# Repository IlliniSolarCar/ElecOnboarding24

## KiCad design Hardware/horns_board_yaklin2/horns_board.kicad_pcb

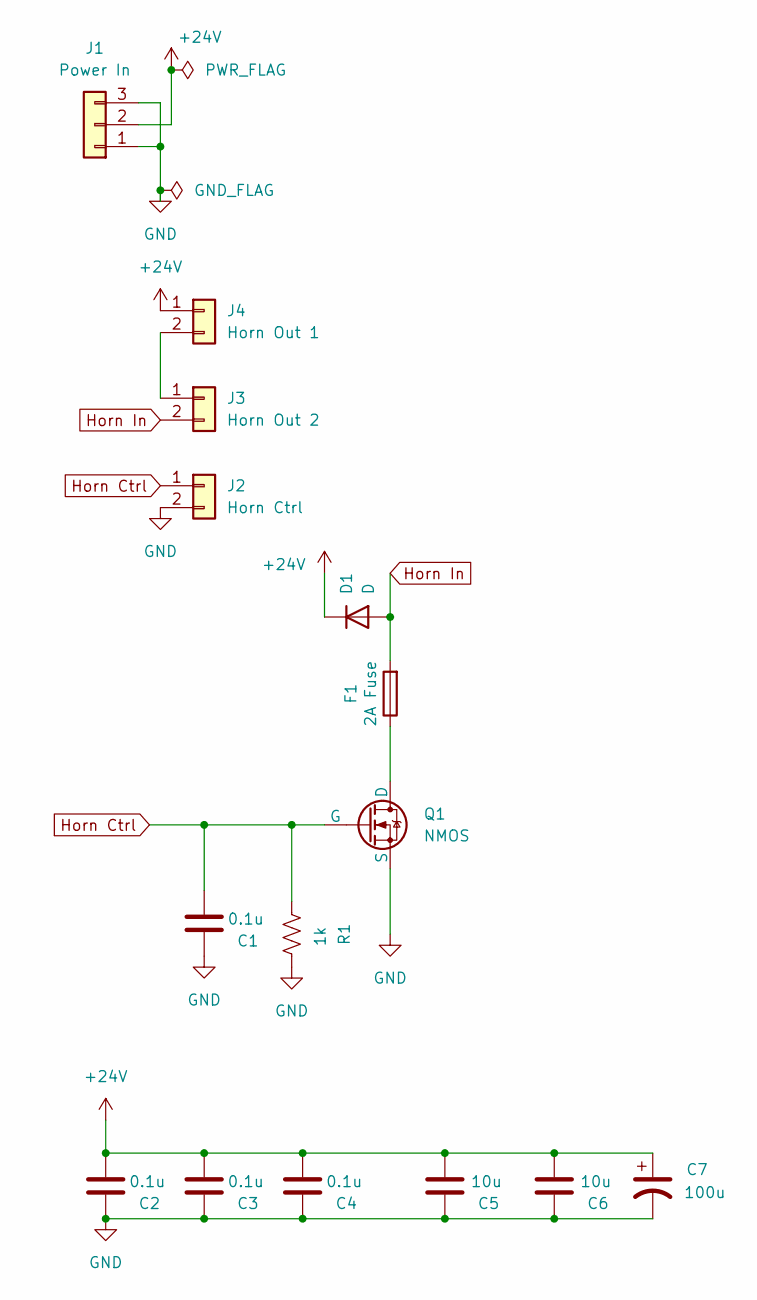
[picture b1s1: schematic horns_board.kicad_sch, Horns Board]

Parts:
C1, C2, C3, C4: 0.1u; C_0603_1608Metric_Pad1.08x0.95mm_HandSolder
C5, C6: 10u; C_0603_1608Metric_Pad1.08x0.95mm_HandSolder
C7: 100u; CP_Radial_Tantal_D6.0mm_P5.00mm
D1: D; D_0201_0603Metric_Pad0.64x0.40mm_HandSolder
F1: 2A Fuse; Fuse_0603_1608Metric_Pad1.05x0.95mm_HandSolder
J1: Power In; Molex_Micro-Fit_3.0_43650-0315_1x03_P3.00mm_Vertical
J2: Horn Ctrl; Molex_Micro-Fit_3.0_43650-0215_1x02_P3.00mm_Vertical
J3: Horn Out 2; Molex_Micro-Fit_3.0_43650-0215_1x02_P3.00mm_Vertical
J4: Horn Out 1; Molex_Micro-Fit_3.0_43650-0215_1x02_P3.00mm_Vertical
Q1: NMOS; TO-252-2
R1: 1k; R_0201_0603Metric_Pad0.64x0.40mm_HandSolder

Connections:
+24V: C2.2, C3.2, C4.2, C5.2, C6.2, C7.1, D1.1 (K), J1.2, J4.1
GND: C1.1, C2.1, C3.1, C4.1, C5.1, C6.1, C7.2, J1.1, J1.3, J2.2, Q1.3 (S), R1.1
Horn Ctrl: C1.2, J2.1, Q1.2 (G), R1.2
Horn In: D1.2 (A), F1.2, J3.2
unnamed: J3.1, J4.2
unnamed: F1.1, Q1.1 (D)

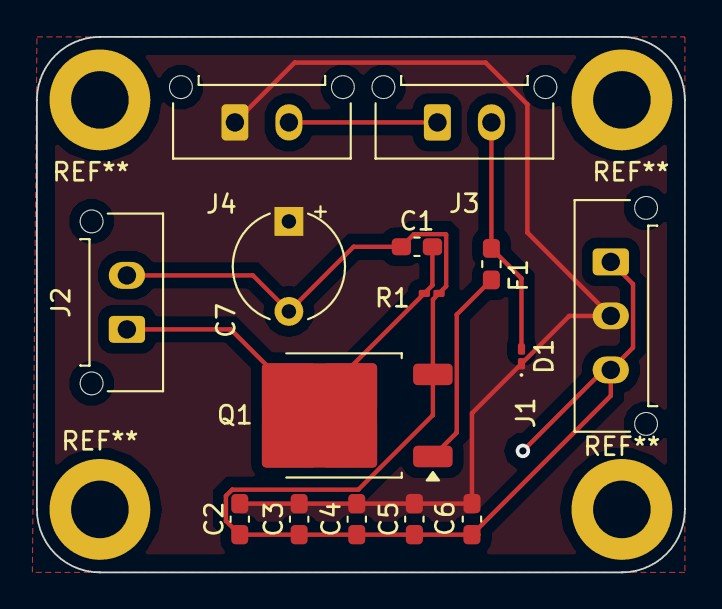
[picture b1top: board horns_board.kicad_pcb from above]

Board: 2 copper layers, 36.0 x 29.8 mm, 15 parts (0 on the bottom side), 6 nets.

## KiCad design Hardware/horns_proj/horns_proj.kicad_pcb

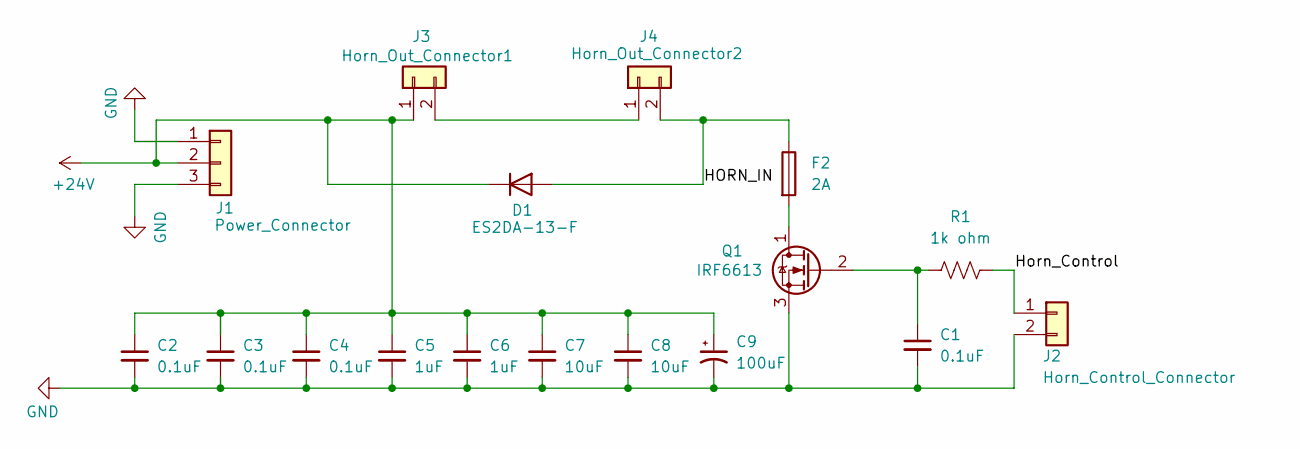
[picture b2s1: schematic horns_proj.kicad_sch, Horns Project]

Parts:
C1, C2, C3, C4: 0.1uF; C_0402_1005Metric_Pad0.74x0.62mm_HandSolder
C5, C6: 1uF; C_0402_1005Metric_Pad0.74x0.62mm_HandSolder
C7, C8: 10uF; C_0504_1310Metric_Pad0.83x1.28mm_HandSolder
C9: 100uF; C_0603_1608Metric_Pad1.08x0.95mm_HandSolder
D1: ES2DA-13-F; D_0402_1005Metric_Pad0.77x0.64mm_HandSolder
F2: 2A; Fuse_1210_3225Metric_Pad1.42x2.65mm_HandSolder
J1: Power_Connector; Molex_KK-254_AE-6410-03A_1x03_P2.54mm_Vertical
J2: Horn_Control_Connector; Molex_KK-254_AE-6410-02A_1x02_P2.54mm_Vertical
J3: Horn_Out_Connector1; Molex_KK-254_AE-6410-02A_1x02_P2.54mm_Vertical
J4: Horn_Out_Connector2; Molex_KK-254_AE-6410-02A_1x02_P2.54mm_Vertical
Q1: IRF6613; DirectFET_MT
R1: 1k ohm; R_0603_1608Metric_Pad0.98x0.95mm_HandSolder

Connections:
+24V: C2.1, C3.1, C4.1, C5.1, C6.1, C7.1, C8.1, C9.1, D1.1 (K), J1.2, J3.1
/HORN_IN: D1.2 (A), F2.1, J4.2
/Horn_Control: J2.1, R1.2
GND: C1.2, C2.2, C3.2, C4.2, C5.2, C6.2, C7.2, C8.2, C9.2, J1.1, J1.3, J2.2, Q1.3 (S)
unnamed: J3.2, J4.1
unnamed: F2.2, Q1.1 (D)
unnamed: C1.1, Q1.2 (G), R1.1

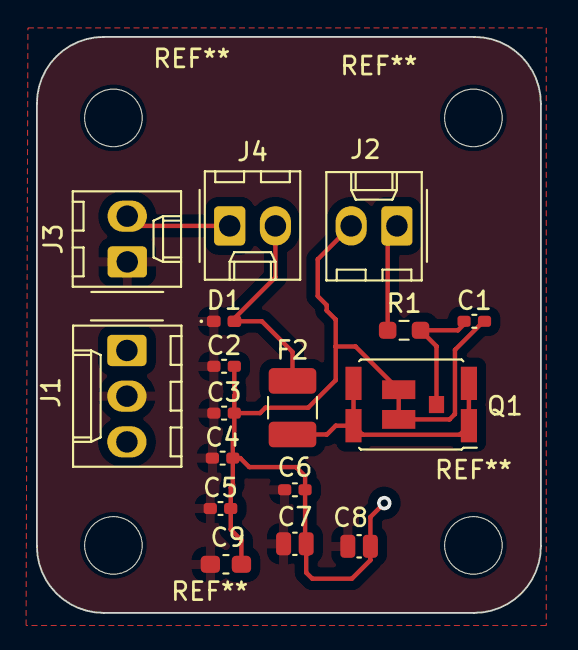
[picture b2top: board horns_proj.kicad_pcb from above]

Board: 2 copper layers, 28.0 x 32.0 mm, 17 parts (0 on the bottom side), 7 nets.

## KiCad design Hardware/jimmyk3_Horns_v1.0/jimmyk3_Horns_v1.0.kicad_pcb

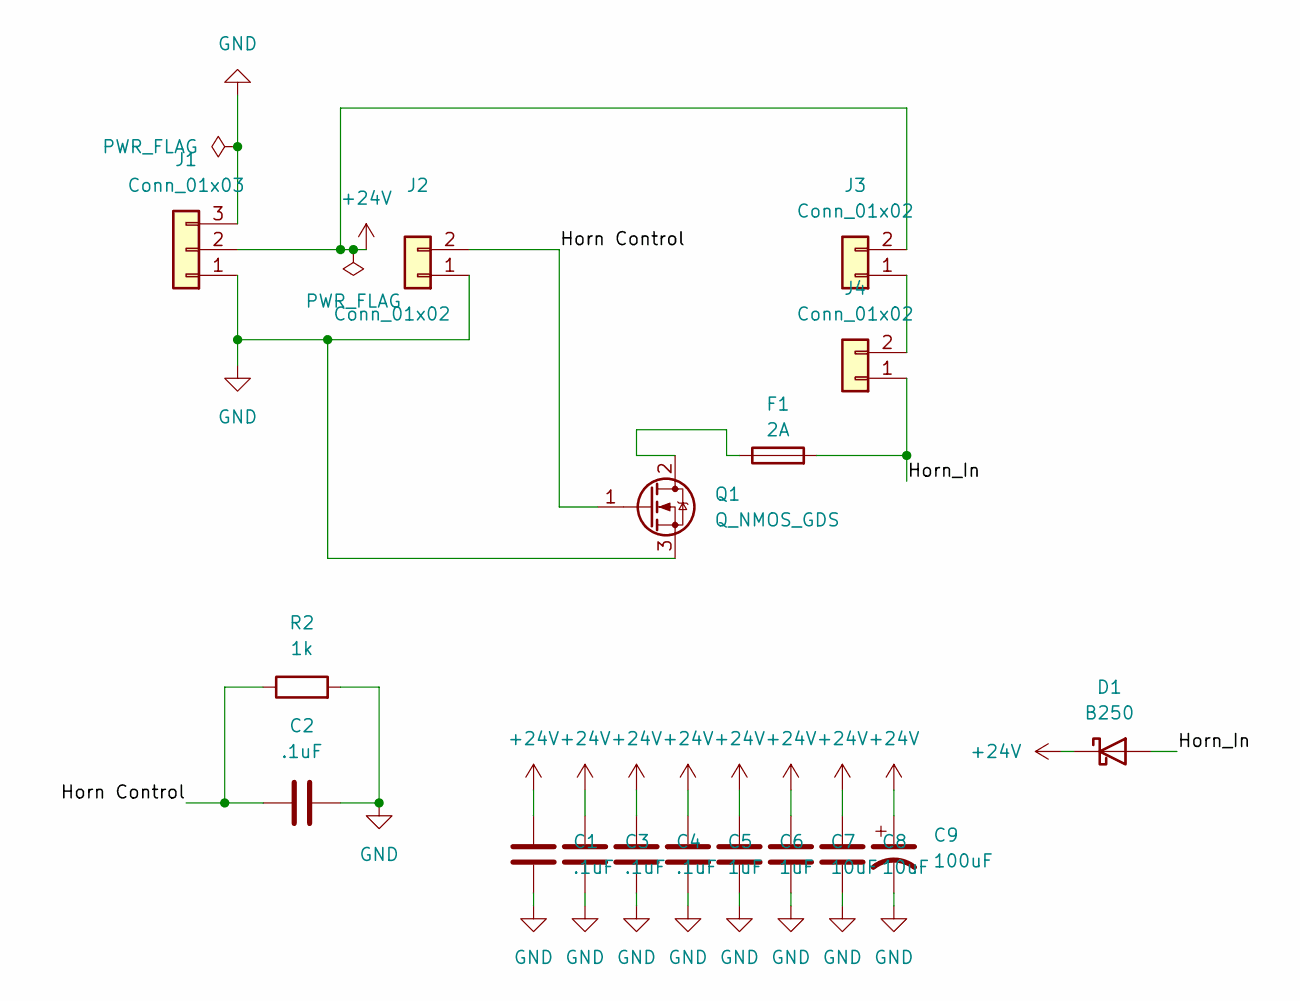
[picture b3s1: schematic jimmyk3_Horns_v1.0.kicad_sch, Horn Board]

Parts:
C1, C2, C3, C4: .1uF; C_0603_1608Metric_Pad1.08x0.95mm_HandSolder
C5, C6: 1uF; C_0603_1608Metric_Pad1.08x0.95mm_HandSolder
C7, C8: 10uF; C_0603_1608Metric_Pad1.08x0.95mm_HandSolder
C9: 100uF; C_0603_1608Metric_Pad1.08x0.95mm_HandSolder
D1: B250; D_0603_1608Metric_Pad1.05x0.95mm_HandSolder; MPN B240-13-F
F1: 2A; Fuse_0603_1608Metric_Pad1.05x0.95mm_HandSolder
J1: Conn_01x03; Molex_KK-254_AE-6410-03A_1x03_P2.54mm_Vertical; MPN 022272021
J2, J3, J4: Conn_01x02; Molex_KK-254_AE-6410-02A_1x02_P2.54mm_Vertical; MPN 022272021
Q1: Q_NMOS_GDS; TO-263-3_TabPin2; MPN sihfr010
R2: 1k; R_0603_1608Metric_Pad0.98x0.95mm_HandSolder

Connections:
+24V: C1.1, C3.1, C4.1, C5.1, C6.1, C7.1, C8.1, C9.1, D1.1 (K), J1.2, J3.2
/Horn Control: C2.1, J2.2, Q1.1 (G), R2.1
/Horn_In: D1.2 (A), F1.2, J4.1
GND: C1.2, C2.2, C3.2, C4.2, C5.2, C6.2, C7.2, C8.2, C9.2, J1.1, J1.3, J2.1, Q1.3 (S), R2.2
unnamed: J3.1, J4.2
unnamed: F1.1, Q1.2 (D)

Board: 2 copper layers, 17 parts (0 on the bottom side), 6 nets, no tracks yet.

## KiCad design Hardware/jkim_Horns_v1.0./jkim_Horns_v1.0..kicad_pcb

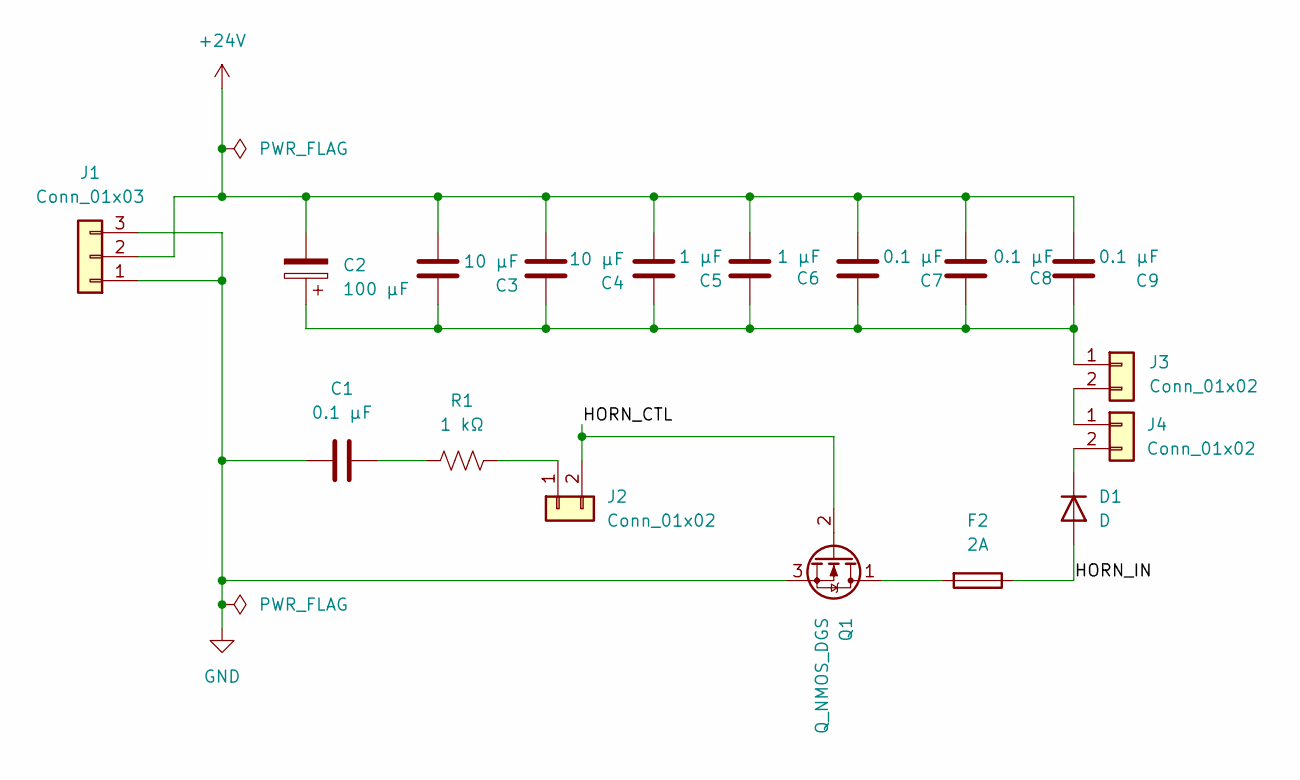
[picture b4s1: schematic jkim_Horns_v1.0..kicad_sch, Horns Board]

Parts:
C1, C7, C8, C9: 0.1 µF; C_0603_1608Metric
C2: 100 µF; C_0603_1608Metric
C3, C4: 10 µF; C_0603_1608Metric
C5, C6: 1 µF; C_0603_1608Metric
D1: D; D_0603_1608Metric_Pad1.05x0.95mm_HandSolder
F2: 2A; D_SOD-123F
J1: Conn_01x03; Molex_Micro-Fit_3.0_43650-0300_1x03_P3.00mm_Horizontal
J2, J3, J4: Conn_01x02; Molex_Micro-Fit_3.0_43650-0200_1x02_P3.00mm_Horizontal
Q1: Q_NMOS_DGS; TO-252-2
R1: 1 kΩ; R_0603_1608Metric_Pad0.98x0.95mm_HandSolder

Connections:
+24V: C2.2, C3.2, C4.2, C5.2, C6.2, C7.2, C8.2, C9.2, J1.2
/HORN_CTL: J2.2, Q1.2 (G)
/HORN_IN: D1.2 (A), F2.1
GND: C1.2, J1.1, J1.3, Q1.3 (S)
unnamed: C1.1, R1.2
unnamed: D1.1 (K), J4.2
unnamed: J2.1, R1.1
unnamed: C2.1, C3.1, C4.1, C5.1, C6.1, C7.1, C8.1, C9.1, J3.1
unnamed: J3.2, J4.1
unnamed: F2.2, Q1.1 (D)

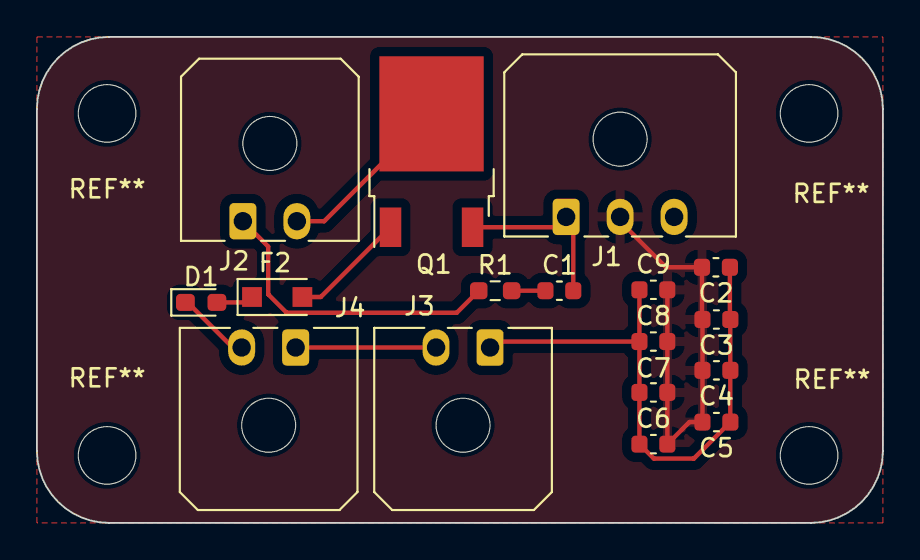
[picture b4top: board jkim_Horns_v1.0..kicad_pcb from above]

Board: 2 copper layers, 47.0 x 27.0 mm, 17 parts (0 on the bottom side), 10 nets.

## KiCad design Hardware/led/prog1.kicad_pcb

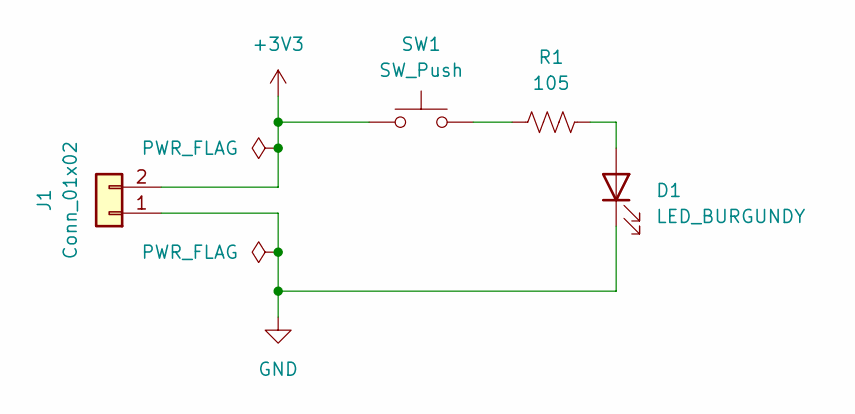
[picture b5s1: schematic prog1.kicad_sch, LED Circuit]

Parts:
D1: LED_BURGUNDY; LED_0603_Symbol_on_F.SilkS
J1: Conn_01x02; Molex_KK-254_AE-6410-02A_1x02_P2.54mm_Vertical; MPN 022272021
R1: 105; R_0603_1608Metric_Pad0.98x0.95mm_HandSolder
SW1: SW_Push; SW_DIP_SPSTx01_Slide_6.7x4.1mm_W8.61mm_P2.54mm_LowProfile; MPN 1825910-6

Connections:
+3V3: J1.2, SW1.1
GND: D1.1 (K), J1.1
unnamed: D1.2 (A), R1.1
unnamed: R1.2, SW1.2

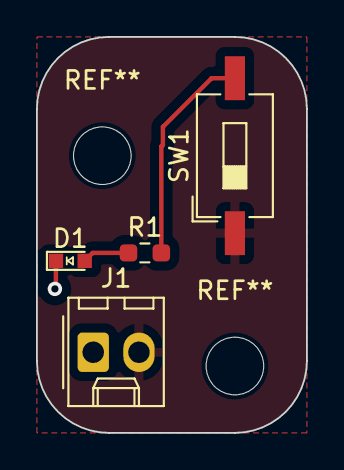
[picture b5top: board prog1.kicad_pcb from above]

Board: 2 copper layers, 15.0 x 22.0 mm, 4 parts (0 on the bottom side), 4 nets.

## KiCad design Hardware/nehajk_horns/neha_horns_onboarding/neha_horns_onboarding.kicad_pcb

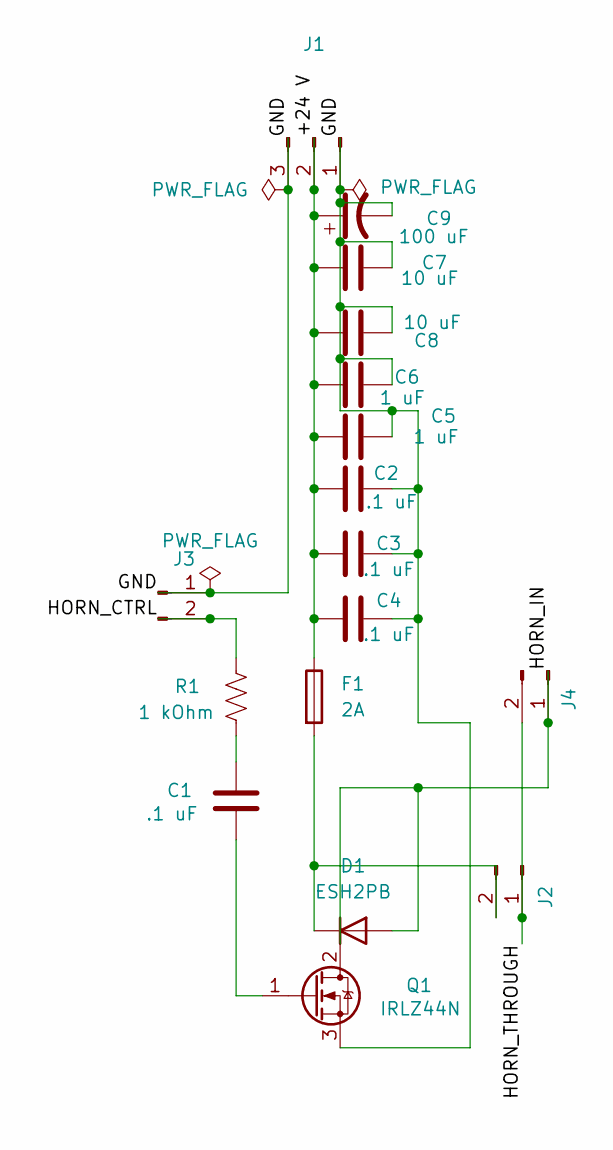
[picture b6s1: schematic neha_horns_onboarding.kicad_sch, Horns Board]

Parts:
C1, C2, C3, C4: .1 uF; C_0603_1608Metric_Pad1.08x0.95mm_HandSolder
C5, C6: 1 uF; C_0603_1608Metric_Pad1.08x0.95mm_HandSolder
C7, C8: 10 uF; C_0603_1608Metric_Pad1.08x0.95mm_HandSolder
C9: 100 uF; C_0603_1608Metric_Pad1.08x0.95mm_HandSolder
D1: ESH2PB; D_0603_1608Metric_Pad1.05x0.95mm_HandSolder
F1: 2A; Fuse_0603_1608Metric_Pad1.05x0.95mm_HandSolder
J1: Conn_01x02_Pin; Molex_Micro-Fit_3.0_43650-0300_1x03_P3.00mm_Horizontal
J2, J3, J4: Conn_01x02_Pin; Molex_Micro-Fit_3.0_43650-0200_1x02_P3.00mm_Horizontal; MPN Molex 22-01-3027
Q1: IRLZ44N; TO-220-3_Vertical
R1: 1 kOhm; R_0603_1608Metric_Pad0.98x0.95mm_HandSolder

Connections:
/+24 V: C2.1, C3.1, C4.1, C5.1, C6.1, C7.2, C8.2, C9.1, F1.1, J1.2
/GND: C2.2, C3.2, C4.2, C5.2, C6.2, C7.1, C8.1, C9.2, J1.1, J1.3, J3.1, Q1.3 (S)
/HORN_CTRL: J3.2, R1.1
/HORN_IN: D1.2 (A), J4.1, Q1.2 (D)
/HORN_THROUGH: J2.1, J4.2
unnamed: C1.1, R1.2
unnamed: D1.1 (K), F1.2, J2.2
unnamed: C1.2, Q1.1 (G)

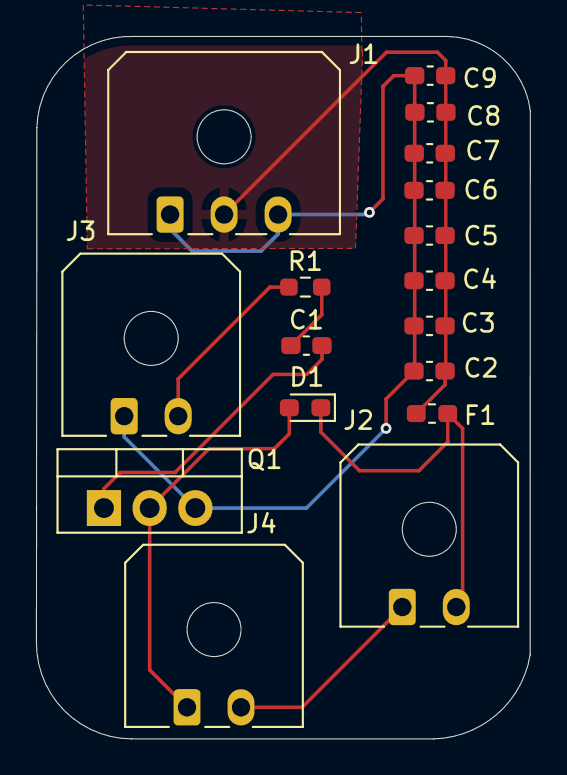
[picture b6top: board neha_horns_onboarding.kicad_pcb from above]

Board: 2 copper layers, 27.4 x 39.0 mm, 17 parts (0 on the bottom side), 8 nets.
